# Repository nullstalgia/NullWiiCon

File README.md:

# NullWiiCon

## What is this?

So, I *love* the Super Nintendo (and SNES Classic) controller, and I love my Nintendo Switch and PC. And while the SN30 wasn't that bad, I wanted something that was wired and worked properly with the Switch Online SNES Emulator. (To use the menu/rewind, you have to press ZL and ZR, and the SN30 only does L and R)

This most recent iteration uses a fork of [CrazyRedMachine](https://github.com/CrazyRedMachine)'s excellent [LUFAHybridFightstick](https://github.com/CrazyRedMachine/LUFAHybridFightstick), modified to interface with Wii's "Extension Controllers" (Classic Controllers and the like) via I2C and [dmadison's](https://github.com/dmadison) wonderful [NintendoExtensionCtrl](https://github.com/dmadison/NintendoExtensionCtrl) library.

## How do I compile this?

1. Download the Arduino IDE (As of writing, I'm using **1.8.16**)
2. Add Arduino-LUFA to the boards manager. [Instructions here.](https://github.com/CrazyRedMachine/Arduino-Lufa) (As of writing, latest is **0.93.0**)
3. With the library manager install `NintendoExtensionCtrl` (As of writing, latest is **0.8.3**)
4. If you're compiling the Slim version, copy the whole `NullWiiCon_Options` folder into your libraries folder.
5. Open the sketch and compile with the `Arduino Micro (LUFA)` profile.
	5. If you get an error complaining about "`{runtime.tools.avr-gcc.path}/bin/avr-g++: no such file or directory`", you're probably running Linux/Mac and need to also install `Arduino AVR Boards` in the Boards Manager. (As of writing, latest is **1.8.3**)

## Todo:

- PCB Pics
- Slim code for V2.1 PCB
- Change "no controller found" LED to all available LEDs

### Thanks to:
- CrazyRedMachine (for allowing my fork and getting Arduino-LUFA to the boards manager!)
- dmadison
- fluffymadness
- progmem
- and others!

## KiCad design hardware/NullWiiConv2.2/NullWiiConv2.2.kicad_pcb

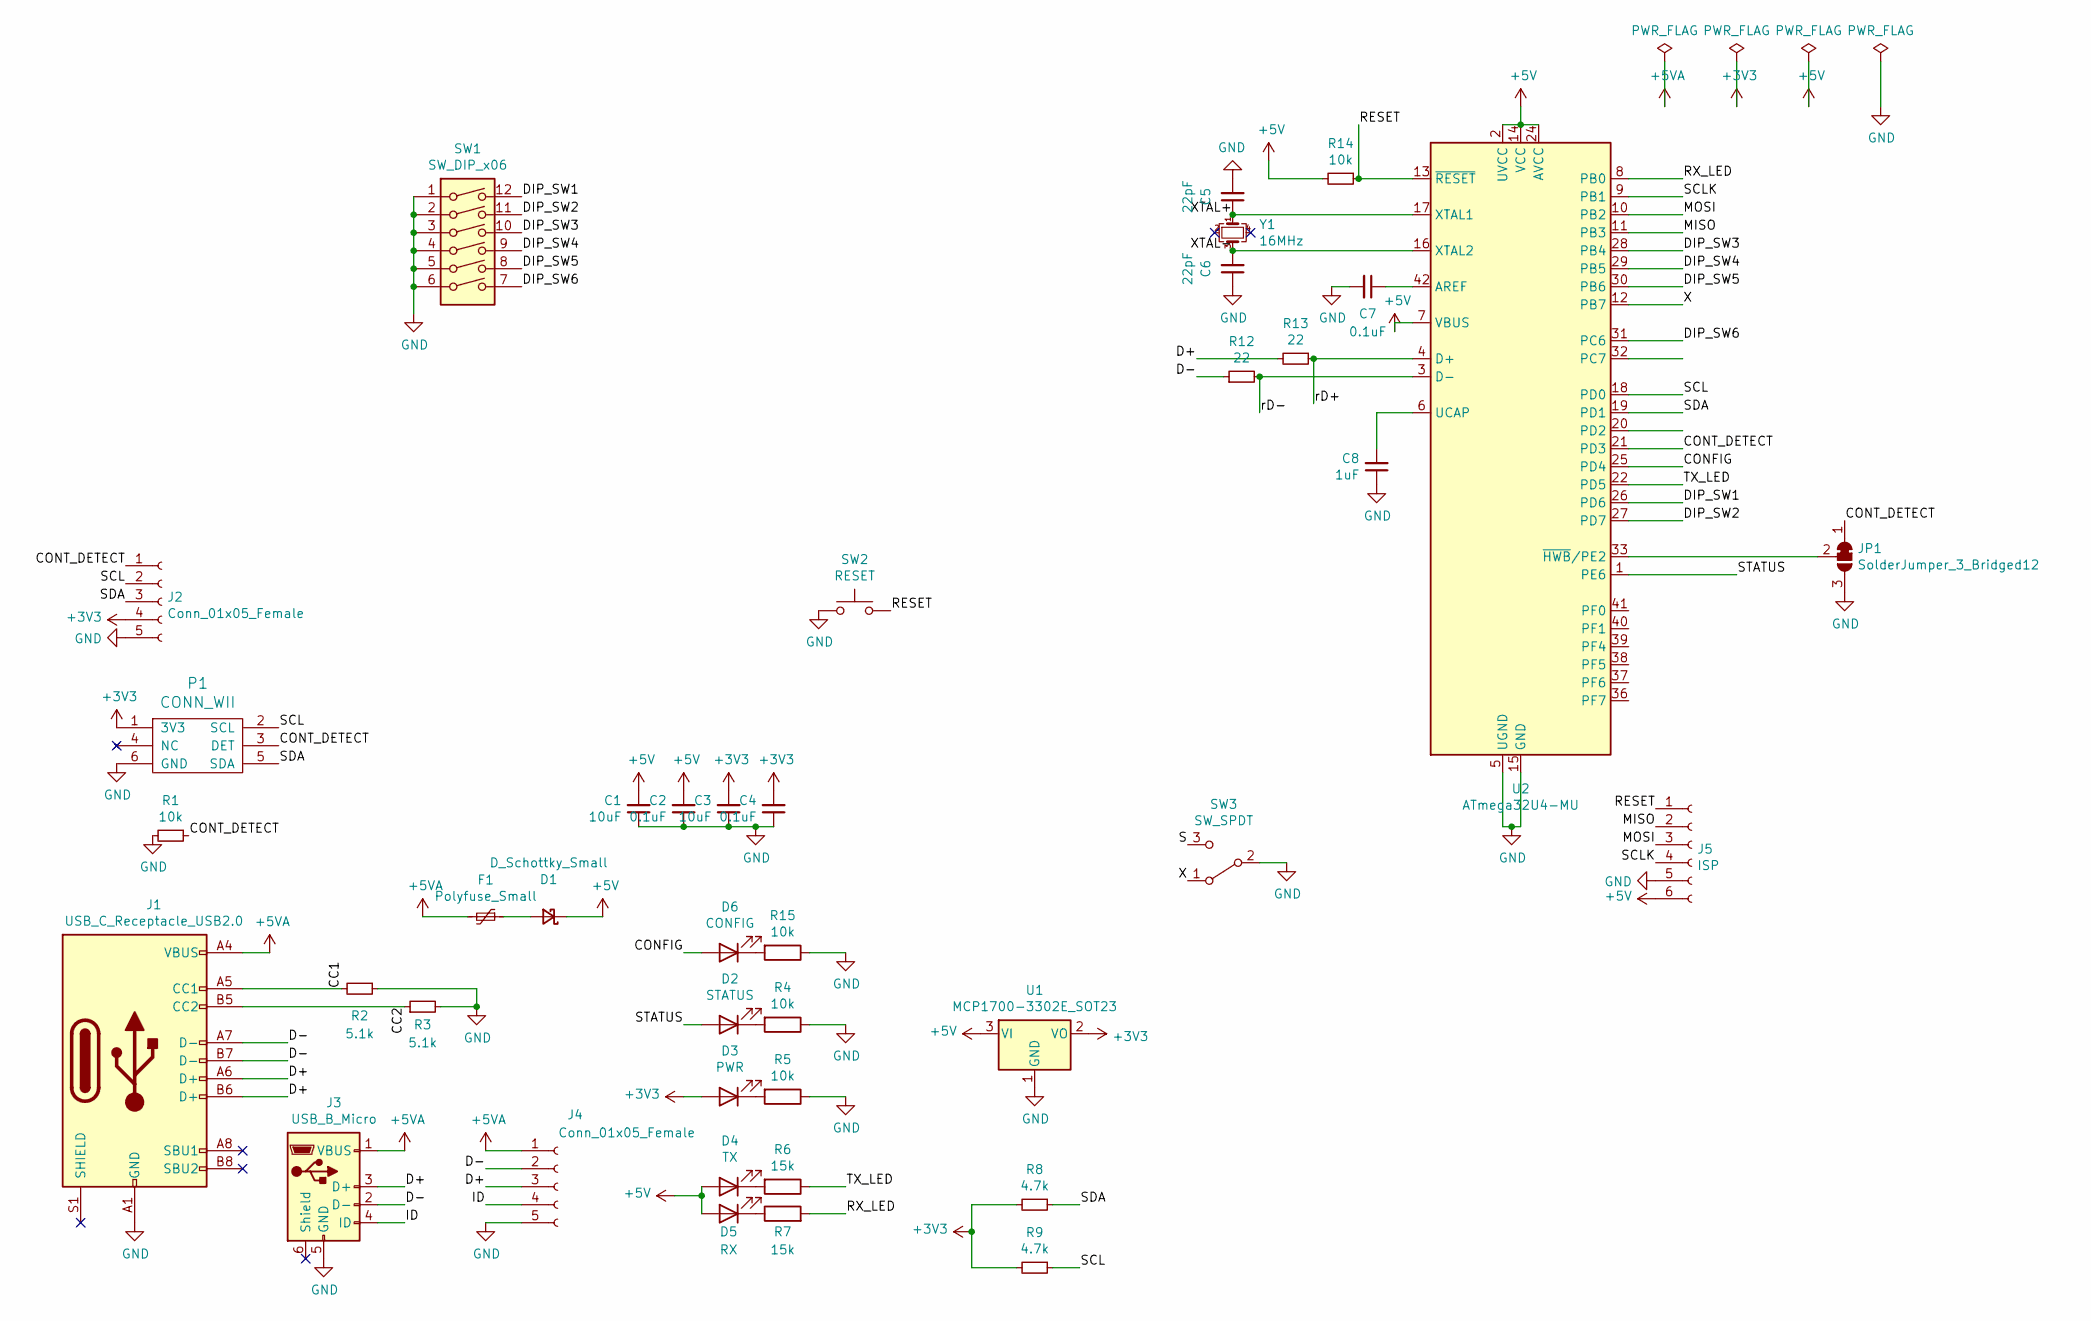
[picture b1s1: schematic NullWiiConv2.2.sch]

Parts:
C1, C3: 10uF; C_0603_1608Metric_Pad1.08x0.95mm_HandSolder; LCSC C19702
C2, C4, C7: 0.1uF; C_0603_1608Metric_Pad1.08x0.95mm_HandSolder; LCSC C14663
C5, C6: 22pF; C_0603_1608Metric_Pad1.08x0.95mm_HandSolder; LCSC C1653
C8: 1uF; C_0603_1608Metric_Pad1.08x0.95mm_HandSolder; LCSC C15849
D1: D_Schottky_Small; D_SOD-123; LCSC C8598
D2: STATUS; LED_0603_1608Metric_Pad1.05x0.95mm_HandSolder; LCSC C72038
D3: PWR; LED_0603_1608Metric_Pad1.05x0.95mm_HandSolder; LCSC C2286
D4: TX; LED_0603_1608Metric_Pad1.05x0.95mm_HandSolder; LCSC C72043
D5: RX; LED_0603_1608Metric_Pad1.05x0.95mm_HandSolder; LCSC C72043
D6: CONFIG; LED_0603_1608Metric_Pad1.05x0.95mm_HandSolder; LCSC C72041
F1: Polyfuse_Small; Fuse_0805_2012Metric_Pad1.15x1.40mm_HandSolder; LCSC C66452
J1: USB_C_Receptacle_USB2.0; HRO-TYPE-C-31-M-12-HandSoldering_ABPads; LCSC C165948
J2, J4: Conn_01x05_Female; PinHeader_1x05_P2.54mm_Vertical
J3: USB_B_Micro; USB_Micro-B_Molex_47346-0001
J5: ISP; 1X06_FEMALE_LOCK.010
JP1: SolderJumper_3_Bridged12; SolderJumper-3_P1.3mm_Bridged12_RoundedPad1.0x1.5mm
P1: CONN_WII
R1, R4, R5, R14, R15: 10k; R_0603_1608Metric_Pad0.98x0.95mm_HandSolder; LCSC C25804
R2, R3: 5.1k; R_0603_1608Metric_Pad0.98x0.95mm_HandSolder; LCSC C23186
R6, R7: 15k; R_0603_1608Metric_Pad0.98x0.95mm_HandSolder; LCSC C22809
R8, R9: 4.7k; R_0603_1608Metric_Pad0.98x0.95mm_HandSolder; LCSC C23162
R12, R13: 22; R_0603_1608Metric_Pad0.98x0.95mm_HandSolder; LCSC C23345
SW1: SW_DIP_x06; SW_DIP_SPSTx06_Slide_9.78x17.42mm_W7.62mm_P2.54mm_NO_MID_SI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
SW2: RESET; SW_SPST_FSMSM; LCSC C118141
SW3: SW_SPDT; PinHeader_1x03_P2.54mm_Vertical
U1: MCP1700-3302E_SOT23; SOT-23; LCSC C39051
U2: ATmega32U4-MU; QFN-44-1EP_7x7mm_P0.5mm_EP5.2x5.2mm_less_midpaste_smaller_E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; LCSC C45874
Y1: 16MHz; Crystal_SMD_3225-4Pin_3.2x2.5mm; LCSC C13738

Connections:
+3V3: C3.2, C4.2, D3.2 (A), J2.4, P1.1 (3V3), R8.2, R9.2, U1.2 (VO)
+5V: C1.2, C2.2, D1.1 (K), D4.2 (A), D5.2 (A), J5.6, R14.2, U1.3 (VI), U2.2 (UVCC), U2.7 (VBUS), U2.14 (VCC), U2.24 (AVCC), U2.34 (VCC), U2.44 (AVCC)
+5VA: F1.2, J1.A4 (VBUS), J1.A9 (VBUS), J1.B4 (VBUS), J1.B9 (VBUS), J3.1 (VBUS), J4.1
/CC1: J1.A5 (CC1), R2.2
/CC2: J1.B5 (CC2), R3.1
/CONFIG: D6.2 (A), U2.25 (PD4)
/CONT_DETECT: J2.1, JP1.1 (A), P1.3 (DET), R1.1, U2.21 (PD3)
/D+: J1.A6 (D+), J1.B6 (D+), J3.3 (D+), J4.3, R13.2
/D-: J1.A7 (D-), J1.B7 (D-), J3.2 (D-), J4.2, R12.1
/DIP_SW1: SW1.12, U2.26 (PD6)
/DIP_SW2: SW1.11, U2.27 (PD7)
/DIP_SW3: SW1.10, U2.28 (PB4)
/DIP_SW4: SW1.9, U2.29 (PB5)
/DIP_SW5: SW1.8, U2.30 (PB6)
/DIP_SW6: SW1.7, U2.31 (PC6)
/ID: J3.4 (ID), J4.4
/MISO: J5.2, U2.11 (PB3)
/MOSI: J5.3, U2.10 (PB2)
/RESET: J5.1, R14.1, SW2.2, U2.13 (~RESET)
/RX_LED: R7.2, U2.8 (PB0)
/S: SW3.3 (C)
/SCL: J2.2, P1.2 (SCL), R9.1, U2.18 (PD0)
/SCLK: J5.4, U2.9 (PB1)
/SDA: J2.3, P1.5 (SDA), R8.1, U2.19 (PD1)
/STATUS: D2.2 (A), U2.1 (PE6)
/TX_LED: R6.1, U2.22 (PD5)
/X: SW3.1 (A), U2.12 (PB7)
/XTAL+: C5.1, U2.17 (XTAL1), Y1.1
/XTAL-: C6.2, U2.16 (XTAL2), Y1.3
/rD+: R13.1, U2.4 (D+)
/rD-: R12.2, U2.3 (D-)
GND: C1.1, C2.1, C3.1, C4.1, C5.2, C6.1, C7.2, C8.1, J1.A1 (GND), J1.A12 (GND), J1.B1 (GND), J1.B12 (GND), J2.5, J3.5 (GND), J4.5, J5.5, JP1.3 (B), P1.6 (GND), R1.2, R2.1, R3.2, R4.1, R5.1, R15.1, SW1.1, SW1.2, SW1.3, SW1.4, SW1.5, SW1.6, SW2.1, SW3.2 (B), U1.1 (GND), U2.5 (UGND), U2.15 (GND), U2.23 (GND), U2.35 (GND), U2.43 (GND), U2.45 (GND)
unnamed: C7.1, U2.42 (AREF)
unnamed: C8.2, U2.6 (UCAP)
unnamed: D1.2 (A), F1.1
unnamed: D2.1 (K), R4.2
unnamed: D3.1 (K), R5.2
unnamed: D4.1 (K), R6.2
unnamed: D5.1 (K), R7.1
unnamed: D6.1 (K), R15.2
unnamed: JP1.2 (C), U2.33 (~HWB~/PE2)

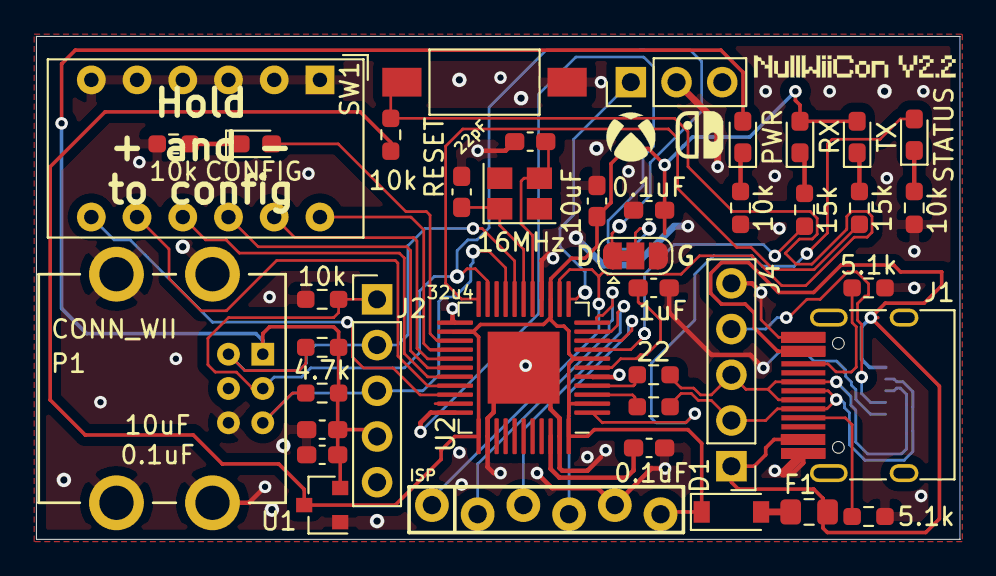
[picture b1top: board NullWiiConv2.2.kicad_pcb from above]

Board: 2 copper layers, 51.3 x 27.9 mm, 41 parts (1 on the bottom side), 40 nets.

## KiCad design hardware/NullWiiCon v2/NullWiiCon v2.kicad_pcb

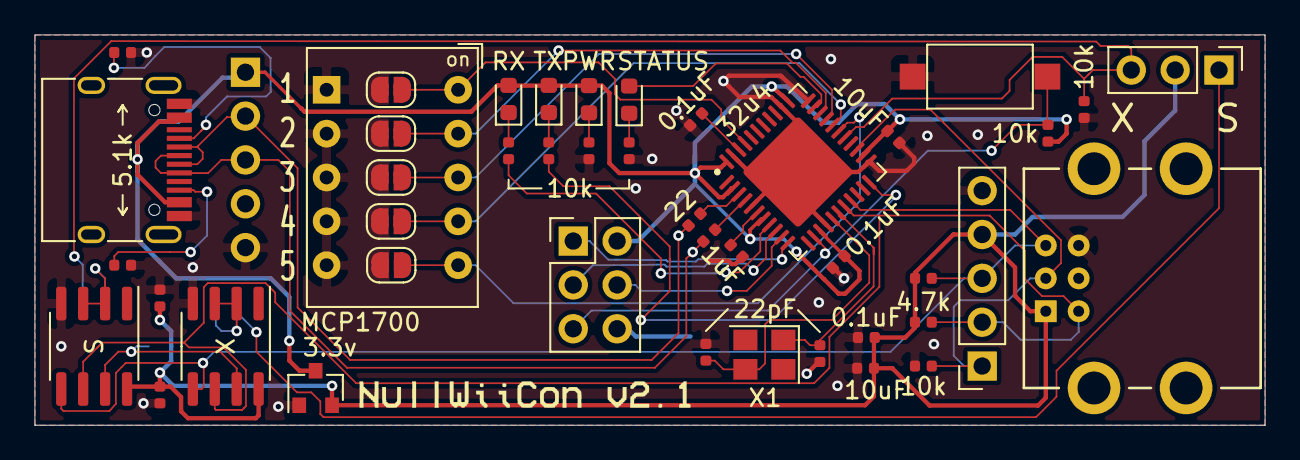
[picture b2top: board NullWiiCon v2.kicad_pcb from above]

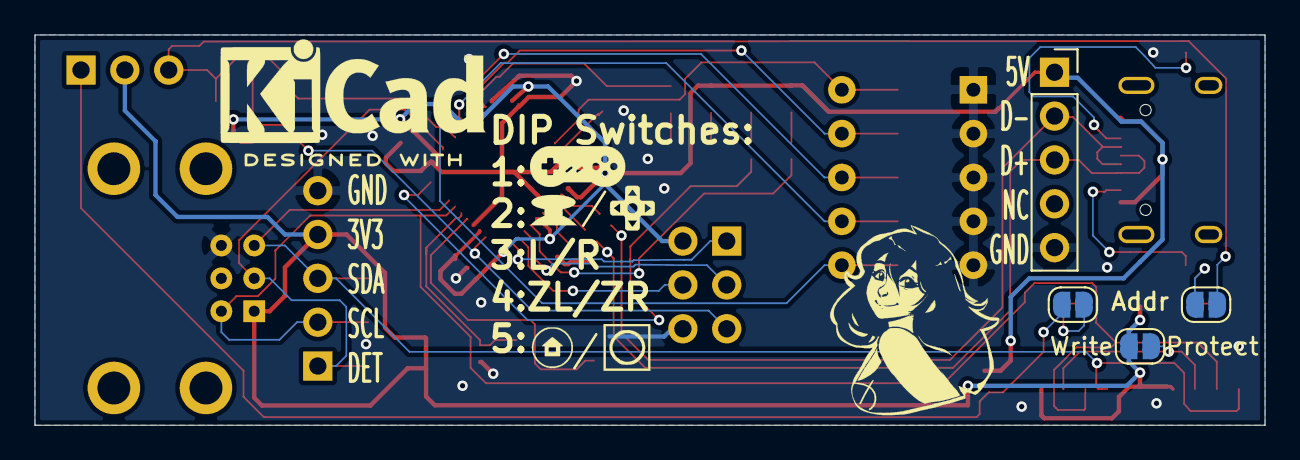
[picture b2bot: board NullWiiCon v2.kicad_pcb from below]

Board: 2 copper layers, 71.2 x 22.6 mm, 48 parts (4 on the bottom side), 37 nets.

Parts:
C1, C3, C9: 10uF; C_0402_1005Metric
C2, C4, C7, C10: 0.1uF; C_0402_1005Metric
C5, C6: 22pF; C_0402_1005Metric
C8: 1uF; C_0402_1005Metric
D1: PWR; LED_0603_1608Metric
D2: TX; LED_0603_1608Metric
D3: RX; LED_0603_1608Metric
D4: STATUS; LED_0603_1608Metric
J1: USB_C_Receptacle_USB2.0; USB_C_Receptacle_HRO_TYPE-C-31-M-12
J2, J4: Conn_01x05_Female; PinSocket_1x05_P2.54mm_Vertical
J5: Conn_02x03_Odd_Even; PinSocket_2x03_P2.54mm_Vertical_MIRROR
J6: Conn_01x03_Female; PinHeader_1x03_P2.54mm_Vertical
JP1, JP2, JP3, JP4, JP5, JP6, JP7, JP9: Jumper; SolderJumper-2_P1.3mm_Open_RoundedPad1.0x1.5mm
P1: CONN_WII
R1, R3, R5, R6, R11, R12, R13: 10k; R_0402_1005Metric
R2, R4: 5.1k; R_0402_1005Metric
R7, R8: 4.7k; R_0402_1005Metric
R9, R10: 22; R_0402_1005Metric
SW1: SW_Push; SW_SPST_CK_RS282G05A3
SW2: SW_DIP_x05; SW_DIP_SPSTx05_Slide_9.78x14.88mm_W7.62mm_P2.54mm
U1: MCP1700-3302E_SOT23; SOT-23
U2: ATmega32U4-MU; QFN-44-1EP_7x7mm_P0.5mm_EP5.2x5.2mm
U3, U4: CAT24C256; SOIC-8_3.9x4.9mm_P1.27mm
X1: Crystal_GND24_Small; Crystal_SMD_3225-4Pin_3.2x2.5mm

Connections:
+3V3: C3.1, C4.1, C9.1, C10.1, J2.4, J6.2, JP9.2, P1.1, R7.2, R8.2, U1.2, U3.8, U4.8
+5V: C1.1, C2.1, D1.2, D2.2, D3.2, J1.A4, J1.A9, J1.B4, J1.B9, J4.1, J5.2, R11.2, U1.3, U2.2, U2.7, U2.14, U2.24, U2.34, U2.44
/CC1: J1.A5, R2.2
/CC2: J1.B5, R4.1
/DETECT: J2.1, P1.3, R1.2, U2.25
/DIP_SW1: JP2.2, SW2.10, U2.41
/DIP_SW2: JP3.2, SW2.9, U2.31
/DIP_SW3: JP4.2, SW2.8, U2.30
/DIP_SW4: JP5.2, SW2.7, U2.29
/DIP_SW5: JP6.2, SW2.6, U2.28
/DN: J1.A7, J1.B7, J4.2, R10.2
/DP: J1.A6, J1.B6, J4.3, R9.2
/MISO: J5.1, U2.11
/MOSI: J5.4, U2.10
/RESET: J5.5, R11.1, SW1.1, U2.13
/RX_LED: R6.1, U2.8
/S: J6.1, JP7.1
/SCL: J2.2, P1.2, R7.1, U2.18, U3.6, U4.6
/SCLK: J5.3, U2.9
/SDA: J2.3, P1.5, R8.1, U2.19, U3.5, U4.5
/STATUS: D4.2, U2.32
/TX_LED: R5.1, U2.22
/WP: JP9.1, U3.7, U4.7
/X: J6.3, JP1.2, R12.1, U2.27
GND: C1.2, C2.2, C3.2, C4.2, C5.1, C6.1, C7.2, C8.2, C9.2, C10.2, J1.A1, J1.A12, J1.B1, J1.B12, J2.5, J4.5, J5.6, JP2.1, JP3.1, JP4.1, JP5.1, JP6.1, P1.6, R1.1, R2.1, R3.1, R4.2, R12.2, R13.1, SW1.2, SW2.1, SW2.2, SW2.3, SW2.4, SW2.5, U1.1, U2.5, U2.15, U2.23, U2.33, U2.35, U2.43, U2.45, U3.4, U4.4
unnamed: C5.2, U2.17, X1.1
unnamed: C6.2, U2.16, X1.3
unnamed: C7.1, U2.42
unnamed: C8.1, U2.6
unnamed: D1.1, R3.2
unnamed: D2.1, R5.2
unnamed: D3.1, R6.2
unnamed: D4.1, R13.2
unnamed: JP1.1, U4.2, U4.3
unnamed: JP7.2, U3.2, U3.3
unnamed: R9.1, U2.4
unnamed: R10.1, U2.3

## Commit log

2020-01-26 Initial Files of v1 and beginning of options lib
2020-01-26 Now comparing v1 and option'd versions
2020-01-26 Separation of v1 and option'd versions
2020-01-26 Updates for all!
2020-01-26 more suitable for copying straight to Arduino folder
2020-01-28 Clamp map() on switch
2020-02-16 Hardware, Bootloader, start of README
2020-02-16 Add GPL
2020-02-19 Huge Switch FW Update, move files around
    In Switch Mode, the Manu and Prod. is changed to Nullstalgia NullWiiCon. Still works on a Switch. Additionally, the stick will report an exact 0 position if it is within 2 of what it was when the ske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
2020-02-20 Update eeprom files
2020-02-21 Rename 'combo' to 'Slim'; more reasonable name
2020-03-04 Move V1 code, add V2 code
2020-03-04 Start of PCB 2.1
2020-03-04 PCB V2.1
2020-03-06 Add beginning of Manual
2020-07-10 Combine XInput and Horipad sketches to switchable descriptor
2020-07-12 Defer emulating <Select> when pressing LR/ZLZR Key
2021-03-24 Add pre-compiled binaries
2021-07-30 Version 2.2 PCB, updated code, moved older stuff
2021-07-30 Readmeme
2021-08-01 Status LED consistency
2021-10-18 Start of V2.1
